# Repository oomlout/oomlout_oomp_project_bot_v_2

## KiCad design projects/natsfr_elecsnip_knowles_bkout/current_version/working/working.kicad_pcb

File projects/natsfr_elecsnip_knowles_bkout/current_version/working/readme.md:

# elecsnip
 
## summary 
* id: natsfr_elecsnip_knowles_bkout
* user: natsfr
* name: elecsnip
* board: knowles_bkout
* repo: https://github.com/natsfr/ElecSnip
* src_file_repo_kicad_pcb: mike/kicad_knowles_bkout/knowles_bkout.kicad_pcb
* src_file_repo_kicad_pcb_link: https://github.com/natsfr/ElecSnip/tree/master/mike/kicad_knowles_bkout/knowles_bkout.kicad_pcb

* src_file_repo_sch: mike/kicad_knowles_bkout/knowles_bkout.sch
* src_file_repo_sch_link: https://github.com/natsfr/ElecSnip/tree/master/mike/kicad_knowles_bkout/knowles_bkout.sch
* full details link: https://github.com/oomlout/oomlout_oomp_project_bot_v_2/tree/main/projects/natsfr_elecsnip_knowles_bkout/current_version/working

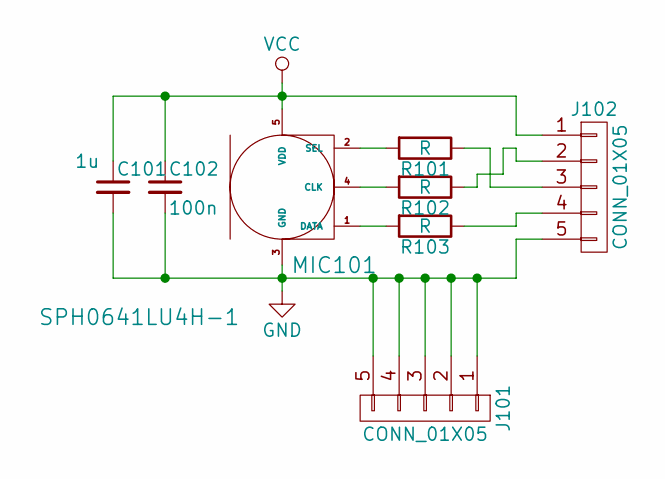
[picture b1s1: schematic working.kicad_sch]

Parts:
C101: 1u; C_0805_HandSoldering
C102: 100n; C_0805_HandSoldering
J101, J102: CONN_01X05; Pin_Header_Straight_1x05_Pitch2.54mm
MIC101: SPH0641LU4H-1
R101, R102, R103: R; R_0603_HandSoldering

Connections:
GND: C101.2, C102.2, J101.1, J101.2, J101.3, J101.4, J101.5, J102.5, MIC101.3 (GND)
unnamed: J102.2, R102.1
unnamed: J102.3, R101.1
unnamed: J102.4, R103.1
unnamed: MIC101.1 (DATA), R103.2
unnamed: MIC101.2 (SEL), R101.2
unnamed: MIC101.4 (CLK), R102.2
VCC: C101.1, C102.1, J102.1, MIC101.5 (VDD)

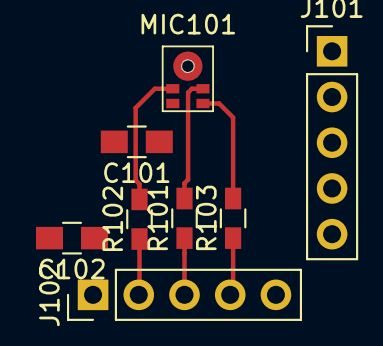
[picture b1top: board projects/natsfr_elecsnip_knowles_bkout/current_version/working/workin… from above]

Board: 2 copper layers, 8 parts (0 on the bottom side), 8 nets.

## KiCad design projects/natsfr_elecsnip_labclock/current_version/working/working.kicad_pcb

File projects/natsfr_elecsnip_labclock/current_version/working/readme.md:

# elecsnip
 
## summary 
* id: natsfr_elecsnip_labclock
* user: natsfr
* name: elecsnip
* board: labclock
* repo: https://github.com/natsfr/ElecSnip
* src_file_repo_kicad_pcb: LabClock/labclock.kicad_pcb
* src_file_repo_kicad_pcb_link: https://github.com/natsfr/ElecSnip/tree/master/LabClock/labclock.kicad_pcb

* src_file_repo_sch: LabClock/labclock.sch
* src_file_repo_sch_link: https://github.com/natsfr/ElecSnip/tree/master/LabClock/labclock.sch
* full details link: https://github.com/oomlout/oomlout_oomp_project_bot_v_2/tree/main/projects/natsfr_elecsnip_labclock/current_version/working

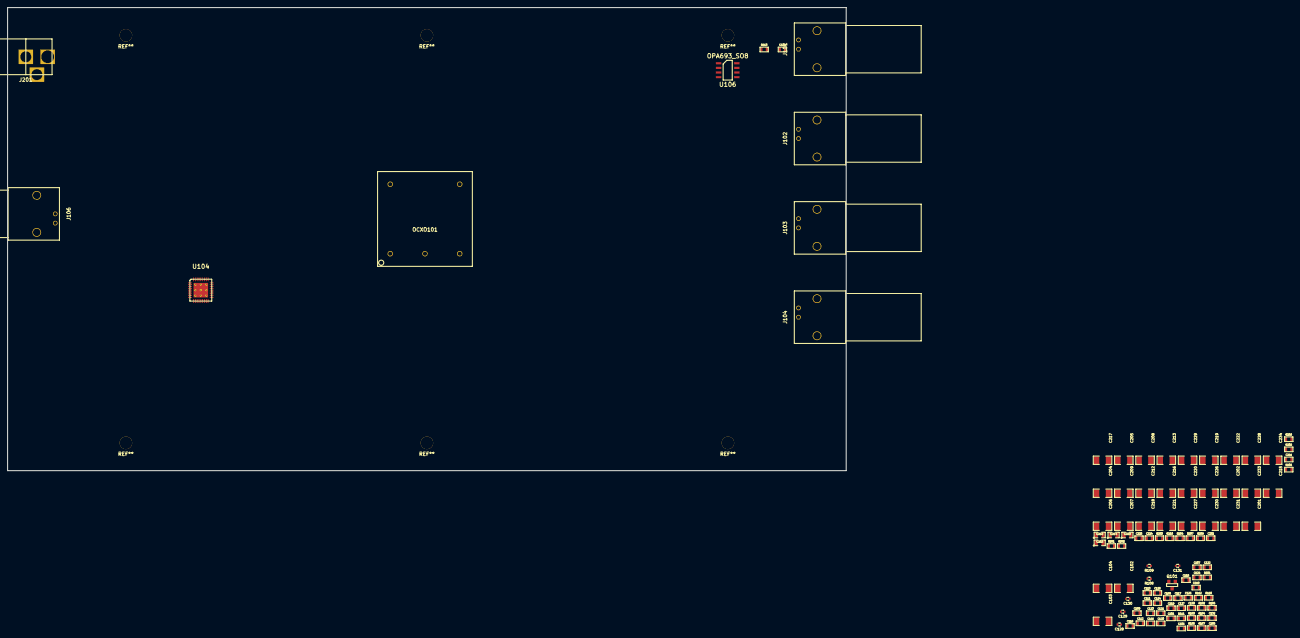
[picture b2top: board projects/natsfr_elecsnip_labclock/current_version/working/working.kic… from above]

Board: 2 copper layers, 230.0 x 127.0 mm, 101 parts (0 on the bottom side), 27 nets, no tracks yet.

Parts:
C101: 1uF; SM0603
C102, C103, C104, C205, C207, C208, C209, C217, C220, C221, C222: 10uF; SM1206
C105: 2uF; SM0603
C106, C109, C110, C111, C112, C116, C119, C121, C123, C124, C127, C133: 100nF; SM0603
C107, C114, C115, C118, C120, C122, C125, C126: 10pF; SM0603
C108, C113, C117: 120pF; SM0603
C128: 1nF; SM0402
C129: 100pF; SM0402
C130, C131: CAP_0402; SM0402
C132: 100pF; SM0603
C134: 10nF; SM0603
C201, C202: 1uF; SM1206
C203, C210, C214, C223: 100nF; SM0805
C204, C206, C212, C213, C215, C216, C218, C219, C226, C227, C228, C229, C230, C231, C233, C234: 10u; SM1206
C211, C224, C225, C232: 1nF; SM0603
J101, J102, J103, J104, J106: BNC; BNC_RHT-610-0048
J201: PJ-002BH-SMT; 2.1mm_DC_Jack_NEB21R_circlehole
OCXO101: NDK_NH26M26LG
Q101: BSS138; SOT23
R101, R111, R112: 1k; SM0603
R102, R103: 100; SM0603
R104: 6k; SM0603
R105, R201, R202, R204, R205, R206, R207, R209, R210: 10k; SM0603
R106: NC; SM0603
R107, R110: 500; SM0603
R108, R109: RES_0402; SM0402
R113: 50; SM0603
R203, R208: 59k; SM0603
U104: STM32F103TB-QFN36; QFN36_6x6_0.5mm
U106: OPA693_SO8; SOIC_8_150mil

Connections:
5V3_OCXO: C203.1, C204.1, C205.1, C206.1, C207.1, R203.2
5V3_PLL: C214.1, C215.1, C216.1, C217.1, C218.1, C219.1, C220.1, C230.1, C231.1, R208.2
5V_AMP: C233.1, C234.1, R111.1, U106.7
5V_OCXO: C101.1, C102.1, C104.1, C212.1, C213.1, OCXO101.5, R101.2
5V_PLL: C106.1, C107.1, C116.1, C118.1, C119.1, C120.1, C121.1, C122.1, C226.1, C228.1
+3.3V: C109.1, C110.1, C111.1, C112.1, C123.1, C124.1, C227.1, C229.1, U104.1, U104.6, U104.19, U104.27
+12V: C103.1, C202.1, C208.1, C209.1, C221.1, C222.1
/MUXOUT: R104.2, R105.1
/OCXO_PW_EN: R201.1, R204.1, R205.1, R206.1, R209.1, R210.1, U104.7
/PLLIN: C132.1, R106.2, R107.2, R110.1
/PLL_VC: C130.1, R109.1
/SINE2AMP: C117.2, C133.1, R106.1
/~PLLSEL: Q101.1, U104.8
GND: C101.2, C102.2, C103.2, C104.2, C105.2, C106.2, C107.2, C109.2, C110.2, C111.2, C112.2, C113.2, C114.1, C115.2, C116.2, C118.2, C119.2, C120.2, C121.2, C122.2, C123.2, C124.2, C125.1, C126.2, C127.2, C129.2, C130.2, C131.2, C201.2, C202.2, C203.2, C204.2, C205.2, C206.2, C207.2, C208.2, C209.2, C211.2, C212.2, C213.2, C214.2, C215.2, C216.2, C217.2, C218.2, C219.2, C220.2, C221.2, C222.2, C224.2, C225.2, C226.2, C227.2, C228.2, C229.2, C230.2, C231.2, C232.2, C233.2, C234.2, J101.2, J101.3, J102.2, J102.3, J103.2, J103.3, J104.2, J104.3, J106.2, J106.3, J201.2, J201.3, OCXO101.2, Q101.2, R103.2, R105.2, R108.2, R110.2, R112.2, R201.2, R202.2, R204.2, R205.2, R206.2, R207.2, R209.2, R210.2, U104.5, U104.18, U104.26, U104.36, U104.37, U106.4
unnamed: C105.1, R102.1
unnamed: C108.1, OCXO101.1, R107.1
unnamed: C114.2, U104.2
unnamed: C115.1, U104.3
unnamed: C128.2, J106.1
unnamed: C131.1, R109.2
unnamed: C133.2, R111.2, R112.1, U106.3
unnamed: C134.1, R113.2
unnamed: C134.2, J101.1
unnamed: C201.1, J201.1
unnamed: R113.1, U106.6
unnamed: R202.1, R203.1
unnamed: R207.1, R208.1

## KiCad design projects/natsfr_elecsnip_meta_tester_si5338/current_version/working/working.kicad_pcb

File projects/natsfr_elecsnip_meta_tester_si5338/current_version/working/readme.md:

# elecsnip
 
## summary 
* id: natsfr_elecsnip_meta_tester_si5338
* user: natsfr
* name: elecsnip
* board: meta_tester_si5338
* repo: https://github.com/natsfr/ElecSnip
* src_file_repo_kicad_pcb: meta_tester/board/meta_tester_si5338.kicad_pcb
* src_file_repo_kicad_pcb_link: https://github.com/natsfr/ElecSnip/tree/master/meta_tester/board/meta_tester_si5338.kicad_pcb

* src_file_repo_sch: meta_tester/board/meta_tester_si5338.sch
* src_file_repo_sch_link: https://github.com/natsfr/ElecSnip/tree/master/meta_tester/board/meta_tester_si5338.sch
* full details link: https://github.com/oomlout/oomlout_oomp_project_bot_v_2/tree/main/projects/natsfr_elecsnip_meta_tester_si5338/current_version/working

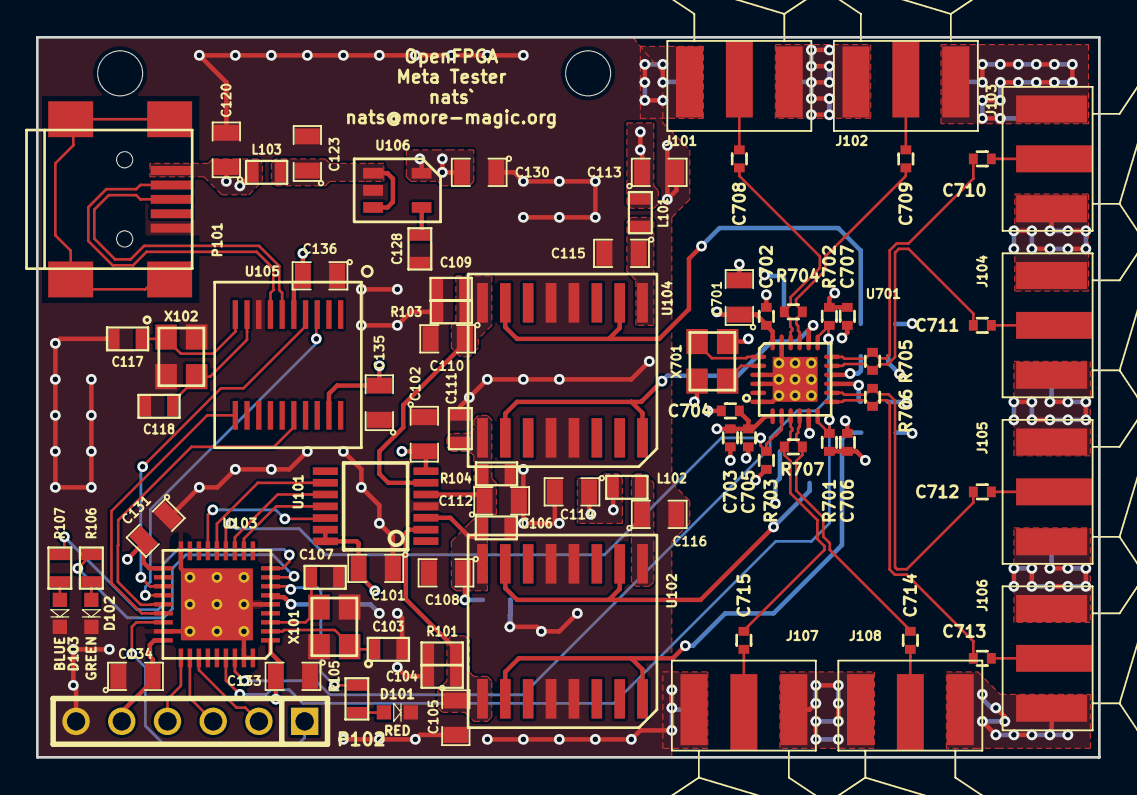
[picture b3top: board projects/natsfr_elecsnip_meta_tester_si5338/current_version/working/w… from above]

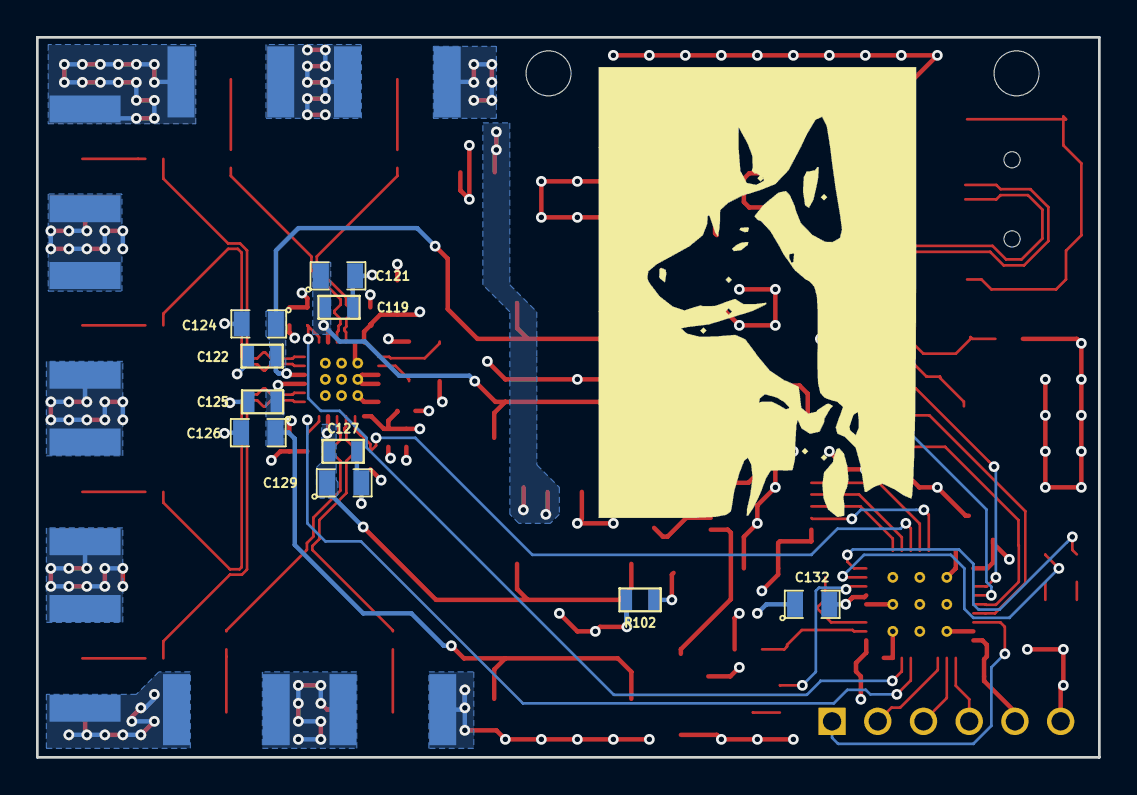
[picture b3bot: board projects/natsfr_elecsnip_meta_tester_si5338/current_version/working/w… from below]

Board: 4 copper layers, 59.0 x 40.0 mm, 91 parts (10 on the bottom side), 60 nets.

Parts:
C101, C102, C131, C132, C133, C134, C135, C136: 100n; SM0805
C103, C107, C117, C118: 10p; SM0603
C104, C106, C109, C111, C119, C122, C125, C127: CAP_0603; SM0603
C105, C108, C110, C112, C121, C124, C126, C129: CAP_0805; SM0805
C113, C114, C115, C116, C120, C123, C130: 1u; SM0805
C128: 10n; SM0603
C701: 10uF; SM0805
C702, C703, C704, C705, C706, C707, C708, C709, C710, C711, C712, C713, C714, C715: 0.1u; SM0402
D101: RED; LED-0603
D102: GREEN; LED-0603
D103: BLUE; LED-0603
J101, J102, J103, J104, J105, J106, J107, J108: SMA_PCB; SMA_AMP_132322
L101, L102, L103: IND_0603; SM0603
P101: USB_OTG; USB_Mini-B
P102: CONN_01X06; pin_array_6x1
R101, R102, R103, R104: 1M; SM0603
R105, R106, R107: RES_0603; SM0603
R701, R702: 10k; SM0402
R703: 4.7k; SM0402
R704, R705, R706, R707: 100; SM0402
U101: MAX5713/4/5-TSSOP14; SSOP14
U102, U104: TCA0372BDW-SOIC16; SOIC-16-10.3x7.5
U103: STM32F103TB-QFN36; QFN36_6x6_0.5mm
U105: CH340T-SSOP20; SSOP-20
U106: REG113-XX-SOT23; SOT23-5
U701: Si5338; QFN24_4x4_9vias
X101: 8MHz; xtal_3.2x2.5
X102: 12MHz; xtal_3.2x2.5
X701: 25MHz; xtal_3.2x2.5

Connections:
+3V3: C101.2, C102.2, C130.2, C131.2, C132.2, C133.2, C134.2, C135.2, C136.2, C701.1, C702.1, C703.1, C704.1, C705.1, C706.1, C707.1, P102.5, R701.1, R702.1, R703.1, U101.7, U101.13, U101.14, U103.1, U103.6, U103.19, U103.27, U105.5, U105.19, U106.5, U701.7, U701.24
+5V: C113.1, C114.1, C120.1, L101.1, L102.1, L103.1, P101.1
/5V01: C123.1, L103.2, U106.1, U106.3
/5338_INT: R703.2, U103.13, U701.8
/CLR_DAC: U101.12, U103.15
/CS_DAC: U101.11, U103.11
/DAC0: C104.1, C105.1, R101.1, U101.2, U102.9
/DAC1: C106.1, C108.1, R102.1, U101.3, U102.8
/DAC2: C109.1, C110.1, R103.1, U101.6, U104.8
/DAC3: C111.1, C112.1, R104.1, U101.5, U104.9
/D_N: P101.2, U105.7
/D_P: P101.3, U105.6
/L_N: C128.2, U106.4
/MOSI_DAC: U101.9, U103.14
/PSU01: C116.1, L102.2, U102.1
/PSU23: C115.1, L101.2, U104.1
/SCK_DAC: U101.10, U103.12
/SCL: R701.2, U103.33, U701.12
/SDA: R702.2, U103.34, U701.19
/SI5338/CLK0_N: C709.2, J102.1
/SI5338/CLK0_P: C708.2, J101.1
/SI5338/CLK1_N: C711.2, J104.1
/SI5338/CLK1_P: C710.2, J103.1
/SI5338/CLK2_N: C713.2, J106.1
/SI5338/CLK2_P: C712.2, J105.1
/SI5338/CLK3_N: C714.2, J108.1
/SI5338/CLK3_P: C715.2, J107.1
/SI5338/clk0_1_N: C709.1, R704.2, U701.21
/SI5338/clk0_1_P: C708.1, R704.1, U701.22
/SI5338/clk1_1_N: C711.1, R705.2, U701.17
/SI5338/clk1_1_P: C710.1, R705.1, U701.18
/SI5338/clk2_1_N: C713.1, R706.2, U701.13
/SI5338/clk2_1_P: C712.1, R706.1, U701.14
/SI5338/clk3_1_N: C715.1, R707.2, U701.9
/SI5338/clk3_1_P: C714.1, R707.1, U701.10
/TCK: P102.4, U103.28
/TDI: P102.3, U103.29
/TDO: P102.2, U103.30
/TMS: P102.1, U103.25
/US1_CTS: U103.23, U105.16
/US1_RTS: U103.24, U105.11
/US1_RX: U103.22, U105.3
/US1_TX: U103.21, U105.4
/VddO0: C119.1, C121.1, U104.10, U104.16, U701.20
/VddO1: C122.1, C124.1, U104.2, U104.7, U701.16
/VddO2: C125.1, C126.1, U102.10, U102.16, U701.15
/VddO3: C127.1, C129.1, U102.2, U102.7, U701.11
GND: C101.1, C102.1, C103.2, C104.2, C105.2, C106.2, C107.2, C108.2, C109.2, C110.2, C111.2, C112.2, C113.2, C114.2, C115.2, C116.2, C117.2, C118.2, C119.2, C120.2, C121.2, C122.2, C123.2, C124.2, C125.2, C126.2, C127.2, C128.1, C129.2, C130.1, C131.1, C132.1, C133.1, C134.1, C135.1, C136.1, C701.2, C702.2, C703.2, C704.2, C705.2, C706.2, C707.2, D101.K, D102.K, D103.K, J101.2, J102.2, J103.2, J104.2, J105.2, J106.2, J107.2, J108.2, P101.5, P102.6, R101.2, R102.2, R103.2, R104.2, U101.4, U102.4, U102.5, U102.12, U102.13, U103.5, U103.18, U103.26, U103.35, U103.36, U103.37, U104.4, U104.5, U104.12, U104.13, U105.8, U106.2, U701.3, U701.4, U701.6, U701.23, U701.25, X101.2, X101.4, X102.2, X102.4, X701.2, X701.4
unnamed: C103.1, U103.2, X101.1
unnamed: C107.1, U103.3, X101.3
unnamed: C117.1, U105.10, X102.1
unnamed: C118.1, U105.9, X102.3
unnamed: D101.A, R105.2
unnamed: D102.A, R106.2
unnamed: D103.A, R107.2
unnamed: R105.1, U103.7
unnamed: R106.1, U103.8
unnamed: R107.1, U103.9
unnamed: U701.1, X701.3
unnamed: U701.2, X701.1

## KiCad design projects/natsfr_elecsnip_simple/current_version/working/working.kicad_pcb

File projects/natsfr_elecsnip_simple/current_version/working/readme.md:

# elecsnip
 
## summary 
* id: natsfr_elecsnip_simple
* user: natsfr
* name: elecsnip
* board: simple
* repo: https://github.com/natsfr/ElecSnip
* src_file_repo_kicad_pcb: HS_Pair_Test/simple/simple.kicad_pcb
* src_file_repo_kicad_pcb_link: https://github.com/natsfr/ElecSnip/tree/master/HS_Pair_Test/simple/simple.kicad_pcb

* src_file_repo_sch: HS_Pair_Test/simple/simple.sch
* src_file_repo_sch_link: https://github.com/natsfr/ElecSnip/tree/master/HS_Pair_Test/simple/simple.sch
* full details link: https://github.com/oomlout/oomlout_oomp_project_bot_v_2/tree/main/projects/natsfr_elecsnip_simple/current_version/working

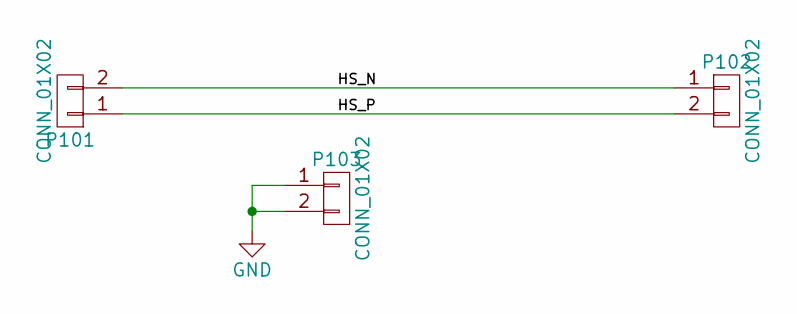
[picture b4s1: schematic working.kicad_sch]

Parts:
P101, P102: CONN_01X02; TEST_01x02_05mm
P103: CONN_01X02; pin_array_2x1

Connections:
/HS_N: P101.2, P102.1
/HS_P: P101.1, P102.2
GND: P103.1, P103.2

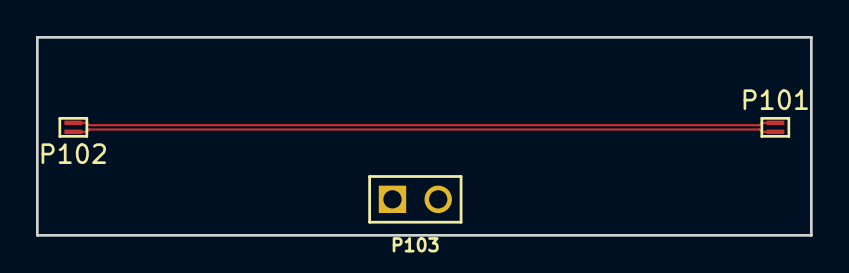
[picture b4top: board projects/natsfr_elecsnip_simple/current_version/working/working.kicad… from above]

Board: 2 copper layers, 43.0 x 11.0 mm, 3 parts (0 on the bottom side), 3 nets.

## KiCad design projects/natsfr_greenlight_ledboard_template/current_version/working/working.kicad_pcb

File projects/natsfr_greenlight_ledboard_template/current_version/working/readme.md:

# greenlight
 
## summary 
* id: natsfr_greenlight_ledboard_template
* user: natsfr
* name: greenlight
* board: ledboard_template
* repo: https://github.com/natsfr/Greenlight
* src_file_repo_kicad_pcb: hardware/LED_Board/LEDBoard_template/LEDBoard_template.kicad_pcb
* src_file_repo_kicad_pcb_link: https://github.com/natsfr/Greenlight/tree/master/hardware/LED_Board/LEDBoard_template/LEDBoard_template.kicad_pcb
* src_file_repo_kicad_sch: hardware/LED_Board/LEDBoard_template/LEDBoard_template.kicad_sch
* src_file_repo_kicad_sch_link: https://github.com/natsfr/Greenlight/tree/master/hardware/LED_Board/LEDBoard_template/LEDBoard_template.kicad_sch

* src_file_repo_sch: 
* src_file_repo_sch_link: https://github.com/natsfr/Greenlight/tree/master/
* full details link: https://github.com/oomlout/oomlout_oomp_project_bot_v_2/tree/main/projects/natsfr_greenlight_ledboard_template/current_version/working

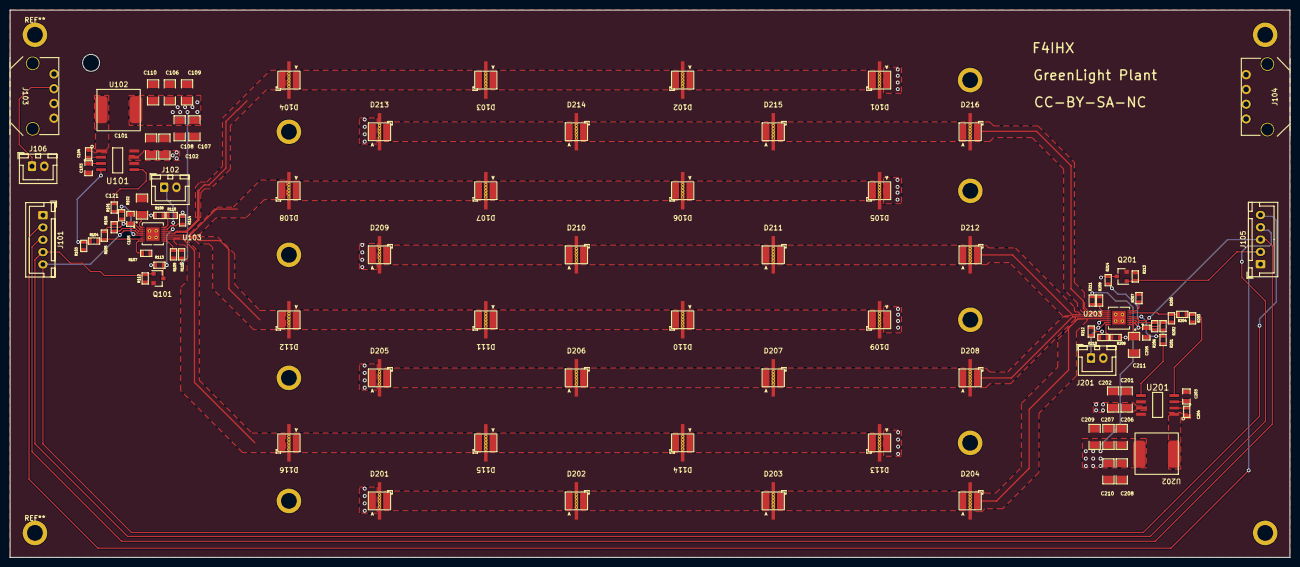
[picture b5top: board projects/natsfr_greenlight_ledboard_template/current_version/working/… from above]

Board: 4 copper layers, 260.0 x 111.2 mm, 97 parts (0 on the bottom side), 68 nets.

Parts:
C101, C102, C121, C201, C202, C211: 4.7uF; SM1206
C103, C105, C203, C205: 1uF; SM0805
C104, C204: 100nF; SM0603
C106, C107, C108, C109, C110, C206, C207, C208, C209, C210: 10uF; SM1206
D101, D102, D103, D104, D105, D106, D107, D108, D109, D110, D111, D112, D113, D114, D115, D116, D202, D203, D204, D206, D207, D208, D210, D211, D212, D214, D215, D216: LED_TPAD; XLamp_MLE
D201, D205, D209, D213: NC; XLamp_MLE
J101, J105: Conn_01x05; JST_XH_B5B-XH-A_1x05_P2.50mm_Vertical
J102, J201: NTC; JST_XH_B2B-XH-A_1x02_P2.50mm_Vertical
J103, J104: Conn_01x04; MICROFIT_4POS_FEM_43650-0403
J106: FAN Connector; JST_XH_B2B-XH-A_1x02_P2.50mm_Vertical
Q101, Q201: BSS138; SOT-23
R101, R110, R201, R210: 0; SM0603
R102, R103, R112, R113, R202, R203, R213, R214: 10k; SM0603
R104, R204: 5k; SM0603
R105, R205: 15k; SM0603
R106, R206: 52.3k; SM0603
R107, R207: 7.32k; SM0603
R108, R114, R208, R212: NC; SM0603
R109, R111, R209, R211: TBD; SM0603
U101, U201: L6982; SOIC-8_208mil
U102, U202: 22uH; IND_SRP8540A_8.1x8.4x3.8mm
U103, U203: ADP8140ACPZ; ADP8140_LFCSP16_4x4_0.4mm

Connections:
+24V: C101.1, C102.1, C121.1, C201.1, C202.1, C211.1, J103.3, J103.4, J104.3, J104.4, J106.1, R108.2, R114.2, R208.2, R212.2, U101.7 (VIN), U103.1 (Vin), U201.7 (VIN), U203.1 (Vin)
/BLUE_PWM: J101.2, J105.2, Q201.1 (G), R213.2
/Blue LEDS/R01: D201.K, D202.A
/Blue LEDS/R02: D202.K, D203.A
/Blue LEDS/R03: D203.K, D204.A
/Blue LEDS/R04: D204.K, U203.13 (SINK1)
/Blue LEDS/R11: D205.K, D206.A
/Blue LEDS/R12: D206.K, D207.A
/Blue LEDS/R13: D207.K, D208.A
/Blue LEDS/R14: D208.K, U203.12 (SINK2)
/Blue LEDS/R21: D209.K, D210.A
/Blue LEDS/R22: D210.K, D211.A
/Blue LEDS/R23: D211.K, D212.A
/Blue LEDS/R24: D212.K, U203.11 (SINK3)
/Blue LEDS/R31: D213.K, D214.A
/Blue LEDS/R32: D214.K, D215.A
/Blue LEDS/R33: D215.K, D216.A
/Blue LEDS/R34: D216.K, U203.10 (SINK4)
/Blue LEDS/RED_FB: R203.1, R204.1, U201.4 (FB)
/Blue LEDS/RSW: C204.1, U201.1 (SW), U202.1
/Blue LEDS/VREG_RED: C205.1, R202.2, R205.1, R214.2, U203.2 (REG)
/Blue LEDS/VRed: C206.1, C207.1, C208.1, C209.1, C210.1, D201.A, D205.A, D209.A, D213.A, R211.1, U202.2
/EN_BLUE: J101.3, J105.3, U203.4 (EN)
/EN_RED: J101.5, J105.5, U103.4 (EN)
/R01: D101.K, D102.A
/R02: D102.K, D103.A
/R03: D103.K, D104.A
/R04: D104.K, U103.13 (SINK1)
/R11: D105.K, D106.A
/R12: D106.K, D107.A
/R13: D107.K, D108.A
/R14: D108.K, U103.12 (SINK2)
/R21: D109.K, D110.A
/R22: D110.K, D111.A
/R23: D111.K, D112.A
/R24: D112.K, U103.11 (SINK3)
/R31: D113.K, D114.A
/R32: D114.K, D115.A
/R33: D115.K, D116.A
/R34: D116.K, U103.10 (SINK4)
/RED_FB: R103.1, R104.1, U101.4 (FB)
/RED_PWM: J101.4, J105.4, Q101.1 (G), R112.2
/RSW: C104.1, U101.1 (SW), U102.1
/VREG_RED: C105.1, R102.2, R105.1, R113.2, U103.2 (REG)
/VRed: C106.1, C107.1, C108.1, C109.1, C110.1, D101.A, D105.A, D109.A, D113.A, R111.1, U102.2
GND: C101.2, C102.2, C103.2, C105.2, C106.2, C107.2, C108.2, C109.2, C110.2, C121.2, C201.2, C202.2, C203.2, C205.2, C206.2, C207.2, C208.2, C209.2, C210.2, C211.2, D101.N (PAD), D102.N (PAD), D103.N (PAD), D104.N (PAD), D105.N (PAD), D106.N (PAD), D107.N (PAD), D108.N (PAD), D109.N (PAD), D110.N (PAD), D111.N (PAD), D112.N (PAD), D113.N (PAD), D114.N (PAD), D115.N (PAD), D116.N (PAD), D201.N (PAD), D202.N (PAD), D203.N (PAD), D204.N (PAD), D205.N (PAD), D206.N (PAD), D207.N (PAD), D208.N (PAD), D209.N (PAD), D210.N (PAD), D211.N (PAD), D212.N (PAD), D213.N (PAD), D214.N (PAD), D215.N (PAD), D216.N (PAD), J101.1, J102.2, J103.1, J103.2, J104.1, J104.2, J105.1, J106.2, J201.2, Q101.2 (S), Q201.2 (S), R103.2, R106.2, R107.2, R109.2, R110.2, R112.1, R203.2, R206.2, R207.2, R209.2, R210.2, R213.1, U101.6 (AGND), U101.8 (PGND), U103.17 (EPAD), U201.6 (AGND), U201.8 (PGND), U203.17 (EPAD)
unnamed: C103.1, U101.3 (VCC)
unnamed: C104.2, U101.2 (BOOT)
unnamed: C203.1, U201.3 (VCC)
unnamed: C204.2, U201.2 (BOOT)
unnamed: J102.1, R114.1, U103.15 (VT)
unnamed: J201.1, R212.1, U203.15 (VT)
unnamed: Q101.3 (D), R113.1, U103.14 (DIM)
unnamed: Q201.3 (D), R214.1, U203.14 (DIM)
unnamed: R101.1, R102.1, U103.5 (~FAULT)
unnamed: R101.2, U101.5 (EN/CLKIN)
unnamed: R104.2, R105.2, U103.7 (COMP)
unnamed: R106.1, U103.3 (MODE)
unnamed: R107.1, U103.8 (ISET)
unnamed: R108.1, R110.1, U103.16 (MIN)
unnamed: R109.1, R111.2, U103.9 (VO_SNS)
unnamed: R201.1, R202.1, U203.5 (~FAULT)
unnamed: R201.2, U201.5 (EN/CLKIN)
unnamed: R204.2, R205.2, U203.7 (COMP)
unnamed: R206.1, U203.3 (MODE)
unnamed: R207.1, U203.8 (ISET)
unnamed: R208.1, R210.1, U203.16 (MIN)
unnamed: R209.1, R211.2, U203.9 (VO_SNS)

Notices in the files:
projects/natsfr_greenlight_ledboard_template/current_version/working/working.kicad_pcb:
CC-BY-SA-NC
